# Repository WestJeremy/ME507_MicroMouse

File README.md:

# ME507_MicroMouse
This repository contains files for a custom PCB and c based code for a micromouse project for ME507 at Cal Poly SLO. This README.md file covers the task diagram and finite state implimentation used for this project.

## TASK DIAGRAM

## FINITE STATE MACHINES
### FloodFill Task
The following finite state machine is implimented for the task that impliments the floodfill algorithm for maze solving. The task begins in an idle state and begins maze solving once it recieves feedback from a start button. States 1-4 perform floodfill depending on the orientation of the micromouse. Micromouse competitions typically start with the robot in the top left corner facing towards the right. so this is what we designated state 1 to be. from there, once floodfill has been completed for a given cell the micromouse is oriented to the neighboring cell with the lowest manhatten distance and the state transitions accordingly.

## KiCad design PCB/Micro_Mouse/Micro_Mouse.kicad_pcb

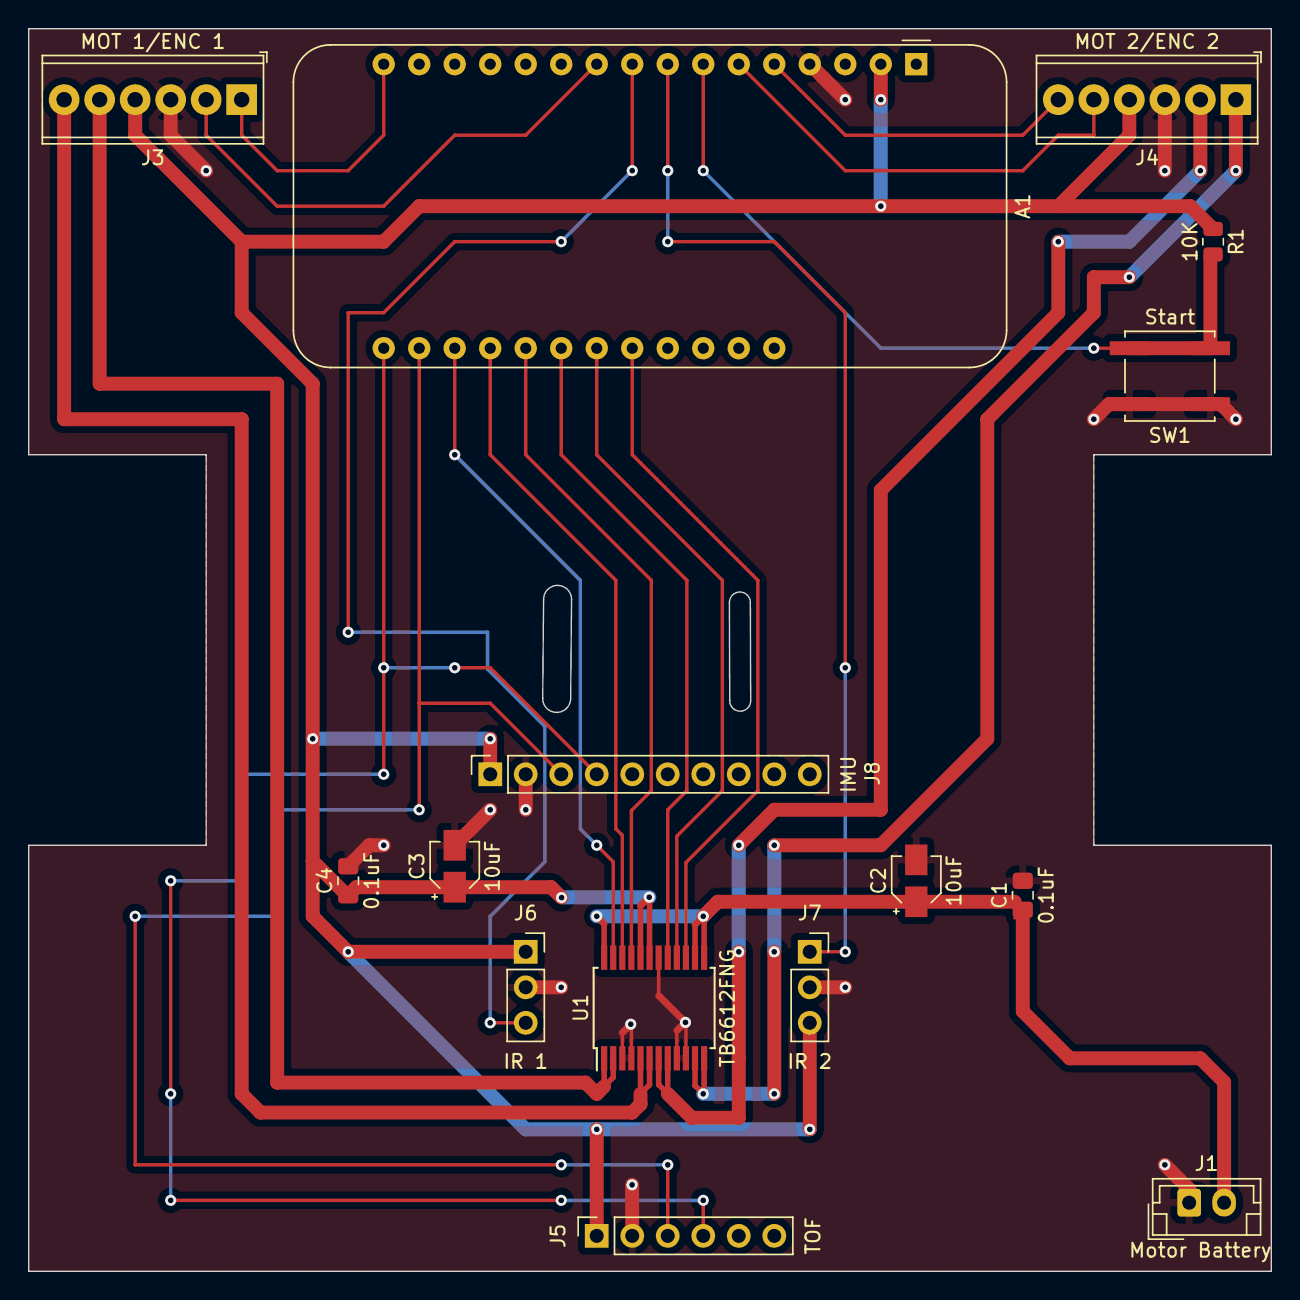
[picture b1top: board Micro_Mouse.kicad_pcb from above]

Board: 2 copper layers, 88.9 x 88.9 mm, 15 parts (0 on the bottom side), 22 nets.

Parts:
A1: Adafruit_Feather_HUZZAH32_ESP32; Adafruit_Feather
C1, C4: 0.1uF; C_0805_2012Metric_Pad1.18x1.45mm_HandSolder
C2, C3: 10uF; CP_Elec_3x5.3
J1: Motor Battery; JST_EH_B2B-EH-A_1x02_P2.50mm_Vertical
J3: MOT 1/ENC 1; TerminalBlock_Phoenix_MPT-0,5-6-2.54_1x06_P2.54mm_Horizontal
J4: MOT 2/ENC 2; TerminalBlock_Phoenix_MPT-0,5-6-2.54_1x06_P2.54mm_Horizontal
J5: TOF; PinSocket_1x06_P2.54mm_Vertical
J6: IR 1; PinSocket_1x03_P2.54mm_Vertical
J7: IR 2; PinSocket_1x03_P2.54mm_Vertical
J8: IMU; PinSocket_1x10_P2.54mm_Vertical
R1: 10K; R_0805_2012Metric
SW1: Start; SW_Push_1P1T_NO_CK_KSC6xxJ
U1: TB6612FNG; SSOP-24_5.3x8.2mm_P0.65mm

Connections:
+3.3V: A1.2 (3V3), C3.1, C4.1, J3.4, J4.4, J5.1, J6.1, J7.3, J8.1, R1.1, U1.19 (STBY), U1.20 (VCC)
AIN1: A1.21 (A8/IO15), U1.21 (AIN1)
AIN2: A1.20 (A7/IO32), U1.22 (AIN2)
AO1: J3.5, U1.1 (AO1), U1.2 (AO1)
AO2: J3.6, U1.5 (AO2), U1.6 (AO2)
BIN1: A1.22 (A9/IO33), U1.17 (BIN1)
BIN2: A1.23 (A10/IO27), U1.16 (BIN2)
BO1: J4.1, U1.11 (BO1), U1.12 (BO1)
BO2: J4.2, U1.7 (BO2), U1.8 (BO2)
BTN: A1.7 (I34/A2), R1.2, SW1.1
E1_PHA: A1.10 (IO4/A5), J3.2
E1_PHB: A1.16 (IO21), J3.1
E2_PHA: A1.6 (DAC1/A1), J4.5
E2_PHB: A1.5 (DAC2/A0), J4.6
GND: A1.4 (GND), C1.2, C2.2, C3.2, C4.2, J1.1, J3.3, J4.3, J5.2, J6.2, J7.2, J8.2, SW1.2, U1.3 (PGND1), U1.4 (PGND1), U1.9 (PGND2), U1.10 (PGND2), U1.18 (GND)
I2C SCL: A1.18 (SCL/IO22), J5.3, J8.3
I2C SDA: A1.17 (SDA/IO23), J5.4, J8.4
IR_1: A1.9 (IO36/A4), J6.3
IR_2: A1.8 (I39/A3), J7.1
unnamed: C1.1, C2.1, J1.2, U1.13 (VM2), U1.14 (VM3), U1.24 (VM1)
PWMA: A1.19 (A6/IO14), U1.23 (PWMA)
PWMB: A1.24 (A11/IO12), U1.15 (PWMB)

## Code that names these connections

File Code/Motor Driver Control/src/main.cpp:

#include <Arduino.h>


 /*
  TB6612FNG-Dual-Driver
  made on 28 oct 2020
  by Amir Mohammad Shojaee @ Electropeak
  Adapted for esp32 feather by Jeremy West 2023
  Home

*/

#define PWM1 15
#define AIN1 33
#define AIN2 27
#define PWM2 4
#define BIN1 5
#define BIN2 18

#define ENCA 32
#define ENCB 14

uint8_t PWMI1=255 ;
uint8_t PWMI2=126 ;

int out;

void setup() {
  Serial.begin(115200);
  pinMode(PWM1,OUTPUT);
  pinMode(AIN1,OUTPUT);
  pinMode(AIN2,OUTPUT);
  pinMode(PWM2,OUTPUT);
  pinMode(BIN1,OUTPUT);
  pinMode(BIN2,OUTPUT);
  pinMode(ENCA,INPUT);
  pinMode(ENCB,INPUT);
  Serial.print("Pins configured");


    
  digitalWrite(AIN1,HIGH); //Motor A Rotate Clockwise
  digitalWrite(AIN2,LOW);
  digitalWrite(BIN1,HIGH); //Motor B Rotate Clockwise
  digitalWrite(BIN2,LOW);

  Serial.print("motor direction configured");

  //pot=analogRead(A0);
  //out=map(pot,0,1023,0,255);
  
  analogWrite(PWM1,PWMI1); //Speed control of Motor A
  analogWrite(PWM2,PWMI2); //Speed control of Motor B
  //Serial.print("good things can happen");
  
  Serial.print("motor speed configured");
  
}
 
void loop() {

digitalWrite(AIN1,HIGH); //Motor A Rotate Clockwise
digitalWrite(AIN2,LOW);

analogWrite(PWM1,PWMI1); //Speed control of Motor A

delay(200);

digitalWrite(AIN1,LOW); //Motor A Rotate Clockwise
digitalWrite(AIN2,HIGH);

analogWrite(PWM1,PWMI1/2); //Speed control of Motor A

Serial.print(digitalRead(ENCA));
delay(200);

}

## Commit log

2023-10-19 added test.txt
2023-10-19 test
2023-11-10 added code under development
2023-11-18 Continued Improvement and debugging of PID control
2023-11-19 P controller now working
2023-11-23 Add files via upload
    contains floodfill and sensor task
2023-12-08 Micromouse operating Coder
    linear and angular movements
2023-12-11 added webserver and delevoped control systems
2023-12-12 Added doxygen comments
2023-12-12 file organization
2023-12-12 Added doxygen documentation
2023-12-12 Formatting
